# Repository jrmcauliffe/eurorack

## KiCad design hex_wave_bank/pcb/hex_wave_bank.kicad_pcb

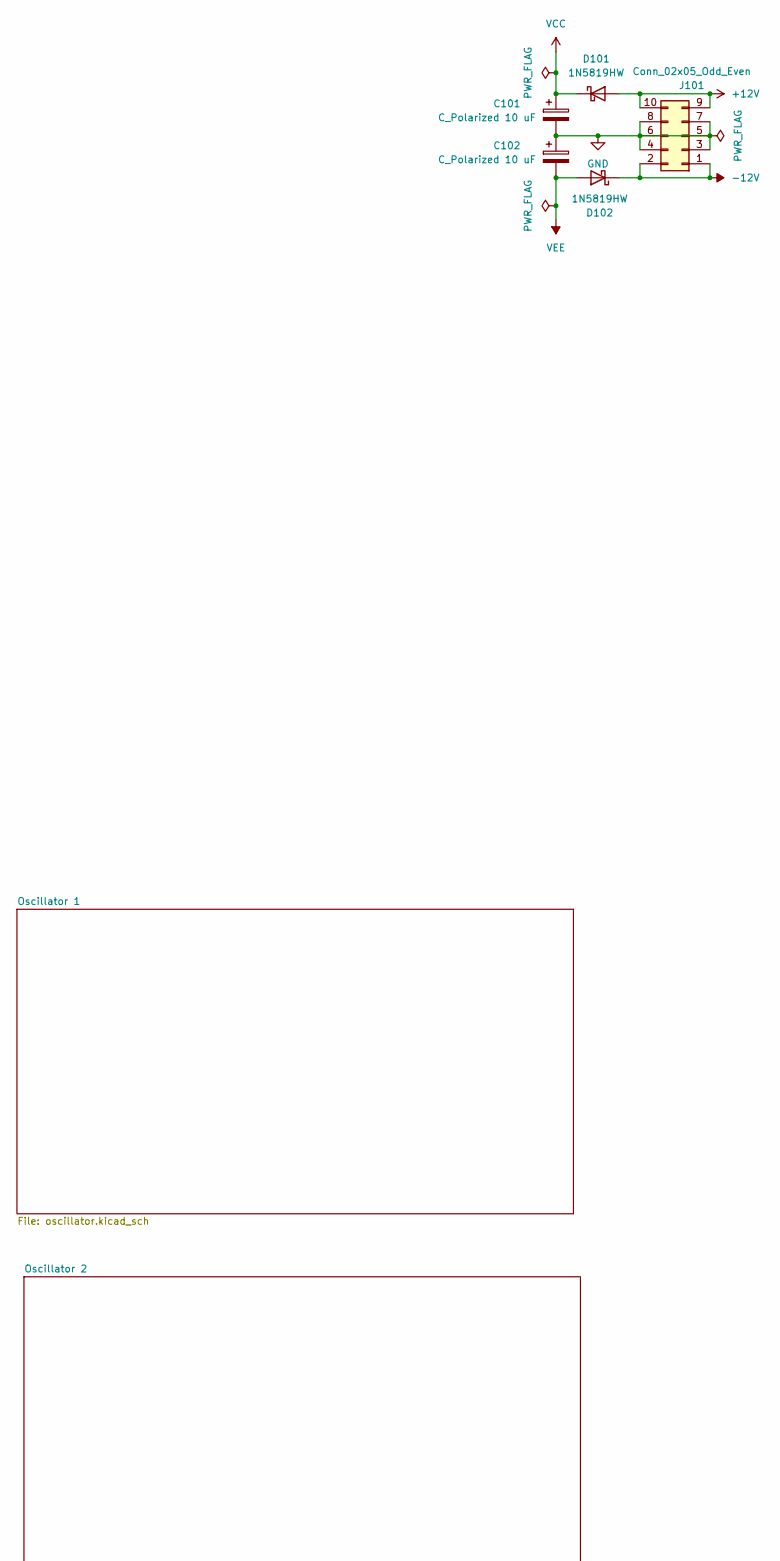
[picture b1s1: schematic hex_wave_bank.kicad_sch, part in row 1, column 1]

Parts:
C101, C102: C_Polarized 10 uF; CP_Elec_4x3
D101, D102: 1N5819HW; D_SOD-123
J101: Conn_02x05_Odd_Even; PinHeader_2x05_P2.54mm_Vertical

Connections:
+12V: D101.2 (A), J101.9, J101.10
-12V: D102.1 (K), J101.1, J101.2
GND: C101.2, C102.1, J101.3, J101.4, J101.5, J101.6, J101.7, J101.8; also elsewhere on the board
VCC: C101.1, D101.1 (K); also elsewhere on the board
VEE: C102.2, D102.2 (A); also elsewhere on the board

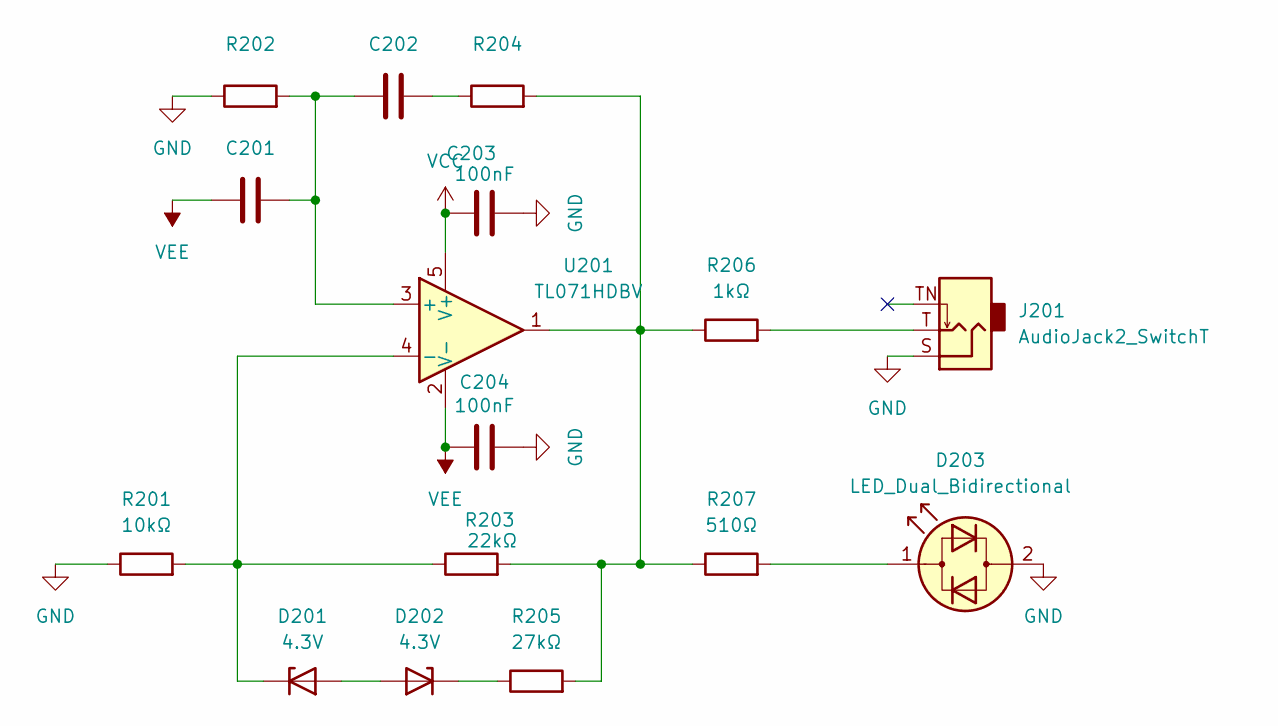
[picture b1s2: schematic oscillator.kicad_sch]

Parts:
C201, C202: C; C_Rect_L7.2mm_W4.5mm_P5.00mm_FKS2_FKP2_MKS2_MKP2
C203, C204: 100nF; C_0603_1608Metric
D201, D202: 4.3V; D_SOD-323_HandSoldering
D203: LED_Dual_Bidirectional; LED_D3.0mm
J201: AudioJack2_SwitchT; Jack_3.5mm_QingPu_WQP-PJ398SM_Vertical_CircularHoles
R201: 10kΩ; R_0603_1608Metric
R202, R204: R_0603_1608Metric
R203: 22kΩ; R_0603_1608Metric
R205: 27kΩ; R_0603_1608Metric
R206: 1kΩ; R_0603_1608Metric
R207: 510Ω; R_0603_1608Metric
U201: TL071HDBV; SOT-23-5

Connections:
GND: C203.2, C204.2, D203.2 (AK), J201.S, R201.1, R202.1; also elsewhere on the board
unnamed: C202.2, R204.1
unnamed: D201.2 (A), D202.2 (A)
unnamed: D201.1 (K), R201.2, R203.1, U201.4 (-)
unnamed: D202.1 (K), R205.1
unnamed: D203.1 (KA), R207.2
unnamed: J201.T, R206.2
unnamed: R203.2, R204.2, R205.2, R206.1, R207.1, U201.1
unnamed: C201.2, C202.1, R202.2, U201.3 (+)
VCC: C203.1, U201.5 (V+); also elsewhere on the board
VEE: C201.1, C204.1, U201.2 (V-); also elsewhere on the board

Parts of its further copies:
C301, C302, C401, C402, C501, C502, C601, C602, C701, C702: C; C_Rect_L7.2mm_W4.5mm_P5.00mm_FKS2_FKP2_MKS2_MKP2
C303, C304, C403, C404, C503, C504, C603, C604, C703, C704: 100nF; C_0603_1608Metric
D301, D302, D401, D402, D501, D502, D601, D602, D701, D702: 4.3V; D_SOD-323_HandSoldering
D303, D403, D503, D603, D703: LED_Dual_Bidirectional; LED_D3.0mm
J301, J401, J501, J601, J701: AudioJack2_SwitchT; Jack_3.5mm_QingPu_WQP-PJ398SM_Vertical_CircularHoles
R301, R401, R501, R601, R701: 10kΩ; R_0603_1608Metric
R302, R304, R402, R404, R502, R504, R602, R604, R702, R704: R_0603_1608Metric
R303, R403, R503, R603, R703: 22kΩ; R_0603_1608Metric
R305, R405, R505, R605, R705: 27kΩ; R_0603_1608Metric
R306, R406, R506, R606, R706: 1kΩ; R_0603_1608Metric
R307, R407, R507, R607, R707: 510Ω; R_0603_1608Metric
U301, U401, U501, U601, U701: TL071HDBV; SOT-23-5

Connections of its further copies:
GND: C303.2, C304.2, C403.2, C404.2, C503.2, C504.2, C603.2, C604.2, C703.2, C704.2, D303.2 (AK), D403.2 (AK), D503.2 (AK), D603.2 (AK), D703.2 (AK), J301.S, J401.S, J501.S, J601.S, J701.S, R301.1, R302.1, R401.1, R402.1, R501.1, R502.1, R601.1, R602.1, R701.1, R702.1; also elsewhere on the board
unnamed: C302.2, R304.1
unnamed: C402.2, R404.1
unnamed: C502.2, R504.1
unnamed: C602.2, R604.1
unnamed: C702.2, R704.1
unnamed: D301.2 (A), D302.2 (A)
unnamed: D301.1 (K), R301.2, R303.1, U301.4 (-)
unnamed: D302.1 (K), R305.1
unnamed: D303.1 (KA), R307.2
unnamed: D401.2 (A), D402.2 (A)
unnamed: D401.1 (K), R401.2, R403.1, U401.4 (-)
unnamed: D402.1 (K), R405.1
unnamed: D403.1 (KA), R407.2
unnamed: D501.2 (A), D502.2 (A)
unnamed: D501.1 (K), R501.2, R503.1, U501.4 (-)
unnamed: D502.1 (K), R505.1
unnamed: D503.1 (KA), R507.2
unnamed: D601.2 (A), D602.2 (A)
unnamed: D601.1 (K), R601.2, R603.1, U601.4 (-)
unnamed: D602.1 (K), R605.1
unnamed: D603.1 (KA), R607.2
unnamed: D701.2 (A), D702.2 (A)
unnamed: D701.1 (K), R701.2, R703.1, U701.4 (-)
unnamed: D702.1 (K), R705.1
unnamed: D703.1 (KA), R707.2
unnamed: J301.T, R306.2
unnamed: J401.T, R406.2
unnamed: J501.T, R506.2
unnamed: J601.T, R606.2
unnamed: J701.T, R706.2
unnamed: R303.2, R304.2, R305.2, R306.1, R307.1, U301.1
unnamed: R403.2, R404.2, R405.2, R406.1, R407.1, U401.1
unnamed: R503.2, R504.2, R505.2, R506.1, R507.1, U501.1
unnamed: R603.2, R604.2, R605.2, R606.1, R607.1, U601.1
unnamed: R703.2, R704.2, R705.2, R706.1, R707.1, U701.1
unnamed: C301.2, C302.1, R302.2, U301.3 (+)
unnamed: C401.2, C402.1, R402.2, U401.3 (+)
unnamed: C501.2, C502.1, R502.2, U501.3 (+)
unnamed: C601.2, C602.1, R602.2, U601.3 (+)
unnamed: C701.2, C702.1, R702.2, U701.3 (+)
VCC: C303.1, C403.1, C503.1, C603.1, C703.1, U301.5 (V+), U401.5 (V+), U501.5 (V+), U601.5 (V+), U701.5 (V+); also elsewhere on the board
VEE: C301.1, C304.1, C401.1, C404.1, C501.1, C504.1, C601.1, C604.1, C701.1, C704.1, U301.2 (V-), U401.2 (V-), U501.2 (V-), U601.2 (V-), U701.2 (V-); also elsewhere on the board

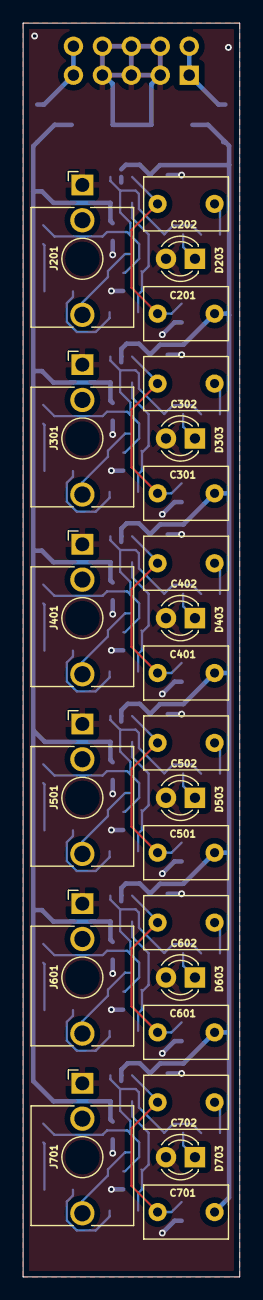
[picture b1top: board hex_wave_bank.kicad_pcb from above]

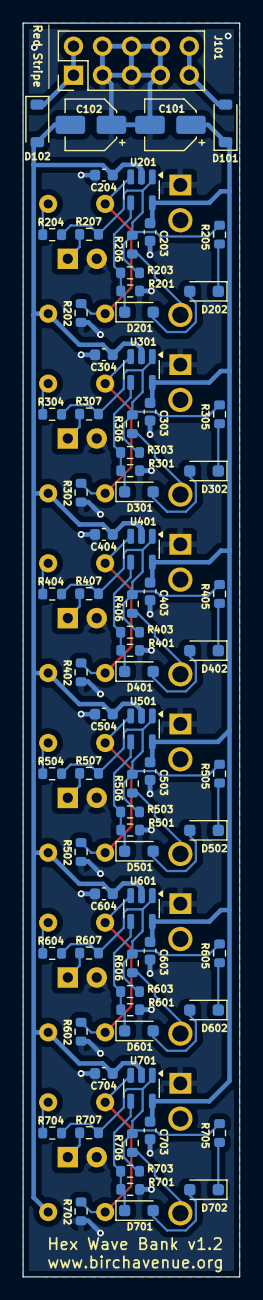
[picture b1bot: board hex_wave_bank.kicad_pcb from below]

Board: 2 copper layers, 19.0 x 110.0 mm, 101 parts (77 on the bottom side), 53 nets.

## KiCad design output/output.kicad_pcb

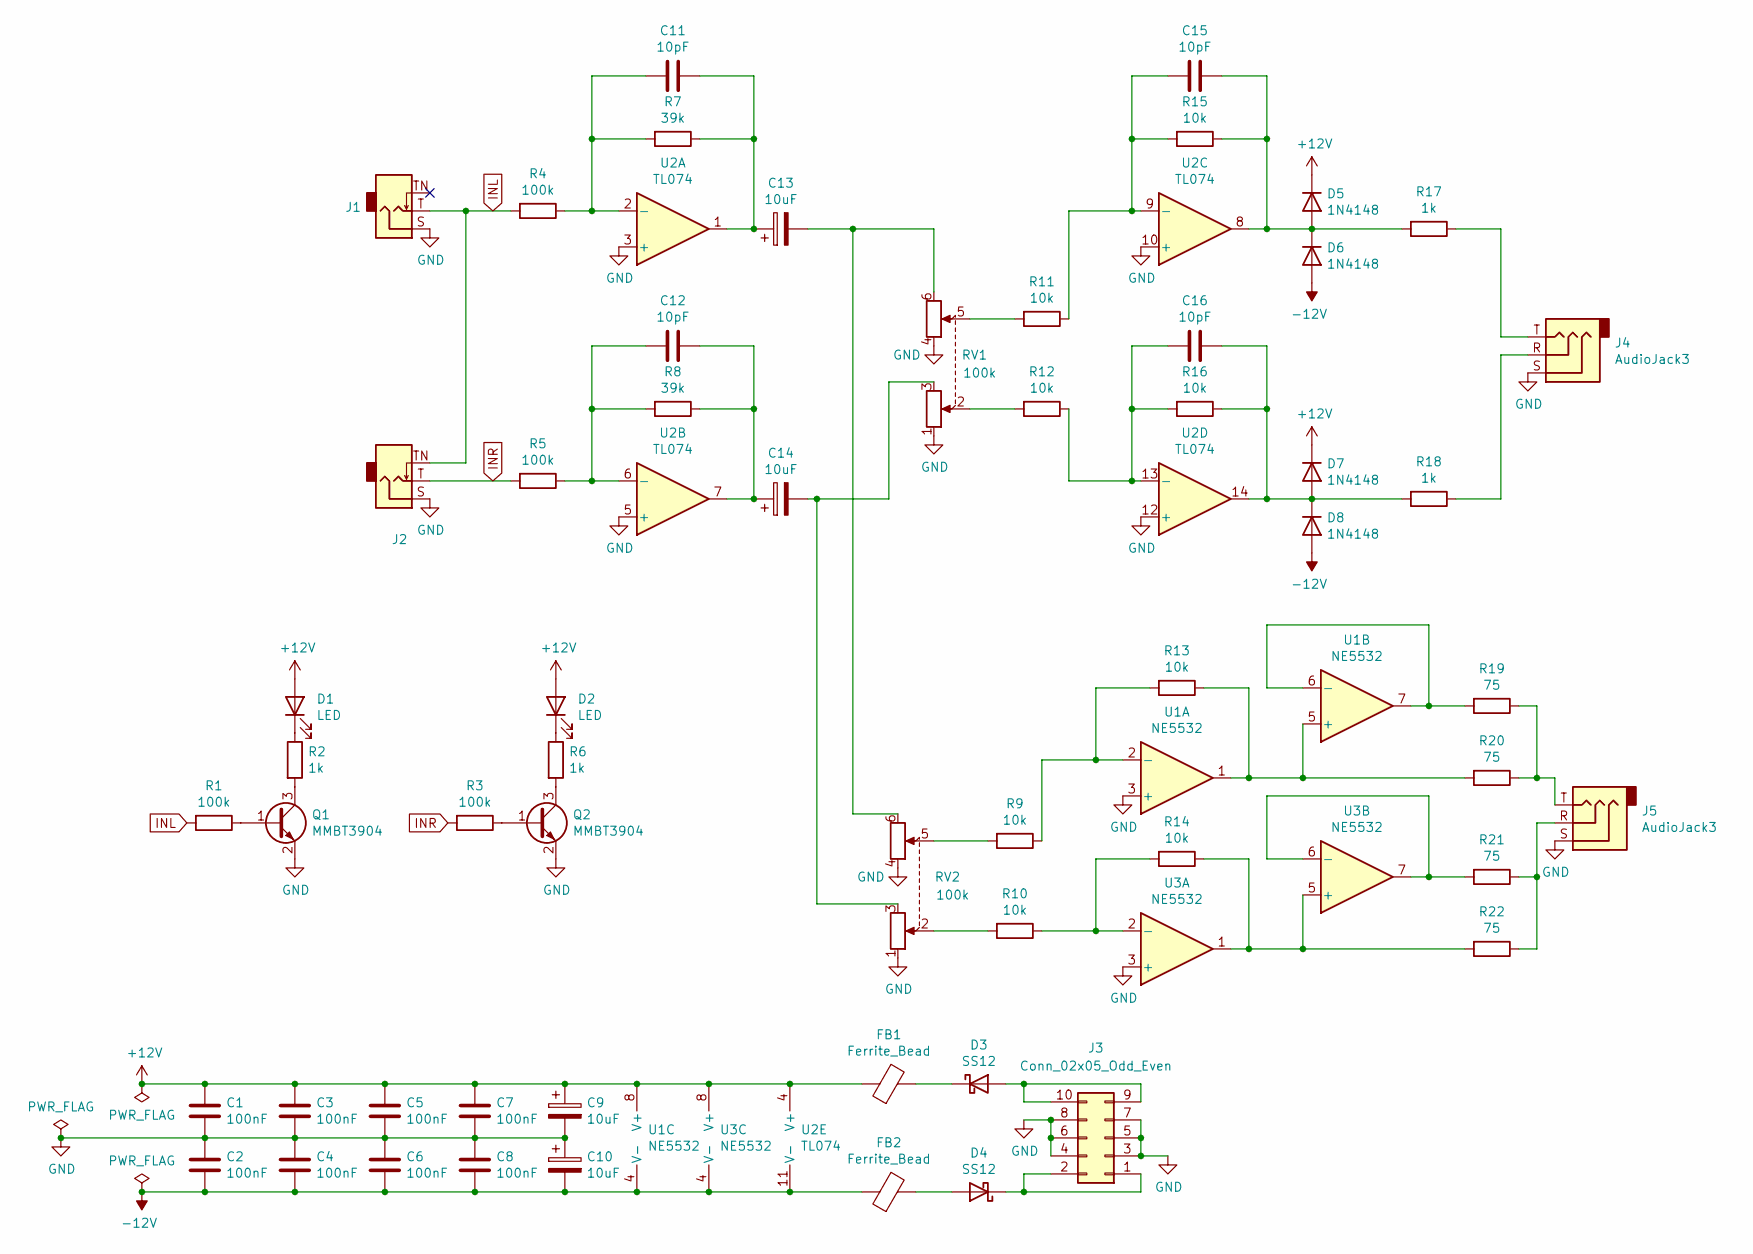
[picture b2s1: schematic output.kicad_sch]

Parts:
C1, C2, C3, C4, C5, C6, C7, C8: 100nF; C_0603_1608Metric_Pad1.05x0.95mm_HandSolder
C9, C10, C13, C14: 10uF; CP_Radial_D4.0mm_P1.50mm
C11, C12, C15, C16: 10pF; C_0603_1608Metric_Pad1.05x0.95mm_HandSolder
D1, D2: LED; LED_D3.0mm
D3, D4: SS12; D_SOD-323_HandSoldering
D5, D6, D7, D8: 1N4148; D_SOD-123
FB1, FB2: Ferrite_Bead; D_0805_2012Metric_Pad1.15x1.40mm_HandSolder
J1, J2: AudioJack2_SwitchT; Jack_3.5mm_QingPu_WQP-PJ398SM_Vertical_CircularHoles
J3: Conn_02x05_Odd_Even; PinHeader_2x05_P2.54mm_Vertical
J4, J5: AudioJack3; Jack_3.5mm_QingPu_WQP-WQP419GR_Vertical_CircularHoles
Q1, Q2: MMBT3904; SOT-23
R1, R3, R4, R5: 100k; R_0603_1608Metric_Pad1.05x0.95mm_HandSolder
R2, R6, R17, R18: 1k; R_0603_1608Metric_Pad1.05x0.95mm_HandSolder
R7, R8: 39k; R_0603_1608Metric_Pad1.05x0.95mm_HandSolder
R9, R10, R11, R12, R13, R14, R15, R16: 10k; R_0603_1608Metric_Pad1.05x0.95mm_HandSolder
R19, R20, R21, R22: 75; R_0603_1608Metric_Pad1.05x0.95mm_HandSolder
RV1, RV2: 100k; Potentiometer_Song_Huei_R1214G_Dual_Vertical
U1, U3: NE5532; SOIC-8_3.9x4.9mm_P1.27mm
U2: TL074; SOIC-14_3.9x8.7mm_P1.27mm

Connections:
+12V: C1.1, C3.1, C5.1, C7.1, C9.1, D1.2 (A), D2.2 (A), D5.1 (K), D7.1 (K), FB1.1, U1.8 (V+), U2.4 (V+), U3.8 (V+)
-12V: C2.2, C4.2, C6.2, C8.2, C10.2, D6.2 (A), D8.2 (A), FB2.1, U1.4 (V-), U2.11 (V-), U3.4 (V-)
GND: C1.2, C2.1, C3.2, C4.1, C5.2, C6.1, C7.2, C8.1, C9.2, C10.1, J1.S, J2.S, J3.3, J3.4, J3.5, J3.6, J3.7, J3.8, J4.S, J5.S, Q1.2 (E), Q2.2 (E), RV1.1, RV1.4, RV2.1, RV2.4, U1.3 (+), U2.3 (+), U2.5 (+), U2.10 (+), U2.12 (+), U3.3 (+)
INL: J1.T, J2.TN, R1.2, R4.2
INR: J2.T, R3.2, R5.2
unnamed: C11.1, C13.1, R7.1, U2.1
unnamed: C11.2, R4.1, R7.2, U2.2 (-)
unnamed: C12.1, C14.1, R8.1, U2.7
unnamed: C12.2, R5.1, R8.2, U2.6 (-)
unnamed: C13.2, RV1.6, RV2.6
unnamed: C14.2, RV1.3, RV2.3
unnamed: C15.1, D5.2 (A), D6.1 (K), R15.1, R17.2, U2.8
unnamed: C15.2, R11.1, R15.2, U2.9 (-)
unnamed: C16.1, D7.2 (A), D8.1 (K), R16.1, R18.2, U2.14
unnamed: C16.2, R12.1, R16.2, U2.13 (-)
unnamed: D1.1 (K), R2.1
unnamed: D2.1 (K), R6.1
unnamed: D3.1 (K), FB1.2
unnamed: D3.2 (A), J3.9, J3.10
unnamed: D4.1 (K), J3.1, J3.2
unnamed: D4.2 (A), FB2.2
unnamed: J4.R, R18.1
unnamed: J4.T, R17.1
unnamed: J5.R, R21.1, R22.1
unnamed: J5.T, R19.1, R20.1
unnamed: Q1.1 (B), R1.1
unnamed: Q1.3 (C), R2.2
unnamed: Q2.1 (B), R3.1
unnamed: Q2.3 (C), R6.2
unnamed: R9.2, RV2.5
unnamed: R10.1, R14.2, U3.2 (-)
unnamed: R10.2, RV2.2
unnamed: R11.2, RV1.5
unnamed: R12.2, RV1.2
unnamed: R13.1, R20.2, U1.1, U1.5 (+)
unnamed: R9.1, R13.2, U1.2 (-)
unnamed: R14.1, R22.2, U3.1, U3.5 (+)
unnamed: R19.2, U1.6 (-), U1.7
unnamed: R21.2, U3.6 (-), U3.7

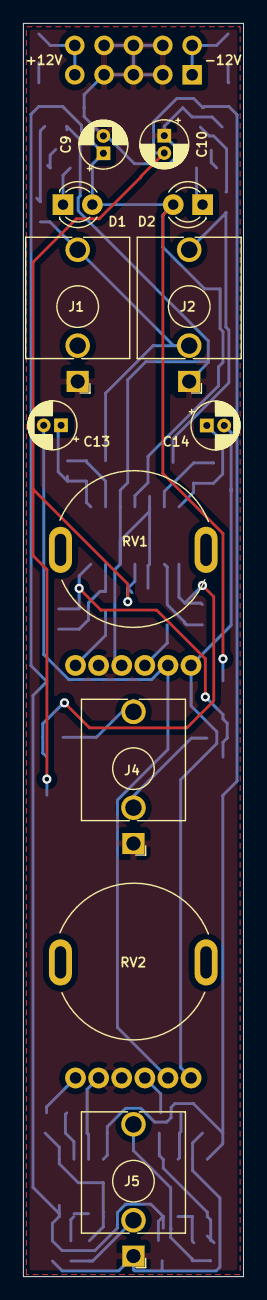
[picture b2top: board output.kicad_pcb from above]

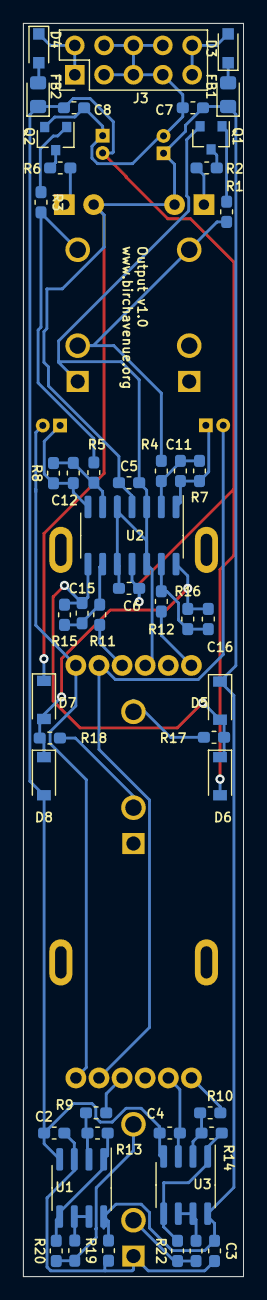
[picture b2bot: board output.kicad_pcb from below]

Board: 2 copper layers, 19.1 x 108.5 mm, 60 parts (48 on the bottom side), 39 nets.

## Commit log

2021-10-20 Board layout for Output module
2021-10-20 Unhide layers
2024-08-08 Update .gitignore for Kicad 8
2024-08-10 Links Panel Desgin
2024-08-10 Remove backups from .gitignore
2024-08-10 Remove idea files and backups
2024-08-10 Ignore editor config files
2024-08-11 First draft of pcb
2024-08-11 Add polarity warning to pcb
2024-08-11 Remove temp files from git and change plot output dir
2024-08-11 Cleanup file
2024-08-11 Relabel ADD as AVG
2024-09-08 Respin PCB for short pcb etc
2024-09-08 Refactor paths for PCB Panel
2024-09-08 Panel working space
2024-09-08 Remove temp file
2024-09-08 Updated panel
2024-09-08 Update plot dirs
2024-09-10 Redo grounds
2024-09-10 Update plotting values
2024-09-10 Kinks panel
2025-01-02 Add another ground plane, add capacitor values
2025-01-02 fix alignment issue with pcb
